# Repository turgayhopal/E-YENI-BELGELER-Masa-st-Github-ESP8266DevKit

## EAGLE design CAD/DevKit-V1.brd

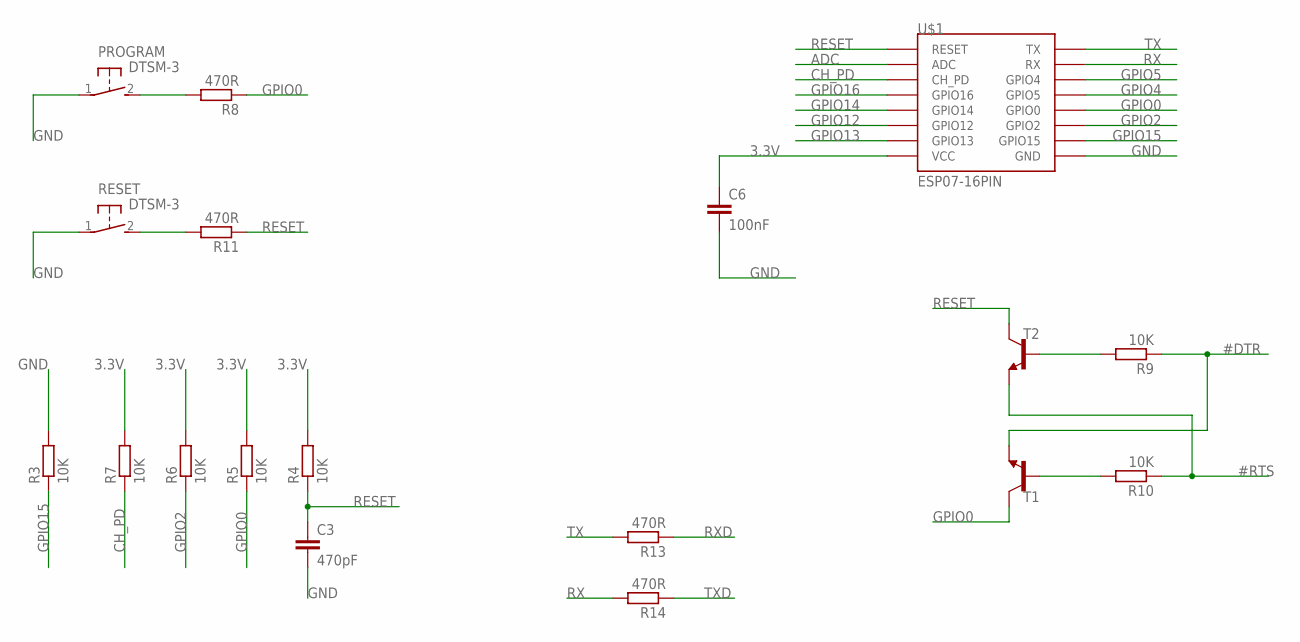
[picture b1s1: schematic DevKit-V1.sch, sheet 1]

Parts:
C3: 470pF; C0805
C6: 100nF; C0805
PROGRAM: DTSM-3
R3, R4, R5, R6, R7, R9, R10: 10K; R0805
R8, R11, R13, R14: 470R; R0805
RESET: DTSM-3
T1, T2: -NPN-SOT23-EBC; SOT23-EBC
U$1: ESP07-16PIN

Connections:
3.3V: C6.1, R4.2, R5.2, R6.2, R7.2, U$1.VCC; also elsewhere on the board
#DTR: R9.1, T1.E; also elsewhere on the board
#RTS: R10.1, T2.E; also elsewhere on the board
ADC: U$1.ADC
CH_PD: R7.1, U$1.CH_PD
GND: C3.2, C6.2, PROGRAM.1, R3.2, RESET.1, U$1.GND; also elsewhere on the board
GPIO0: R5.1, R8.1, T1.C, U$1.GPIO0
GPIO2: R6.1, U$1.GPIO2
GPIO4: U$1.GPIO5; also elsewhere on the board
GPIO5: U$1.GPIO4; also elsewhere on the board
GPIO12: U$1.GPIO12; also elsewhere on the board
GPIO13: U$1.GPIO13; also elsewhere on the board
GPIO14: U$1.GPIO14; also elsewhere on the board
GPIO15: R3.1, U$1.GPIO15; also elsewhere on the board
GPIO16: U$1.GPIO16
unnamed: PROGRAM.2, R8.2
unnamed: R11.2, RESET.2
unnamed: R10.2, T1.B
unnamed: R9.2, T2.B
RESET: C3.1, R4.1, R11.1, T2.C, U$1.REST (RESET)
RX: R14.2, U$1.RX
RXD: R13.1; also elsewhere on the board
TX: R13.2, U$1.TX
TXD: R14.1; also elsewhere on the board

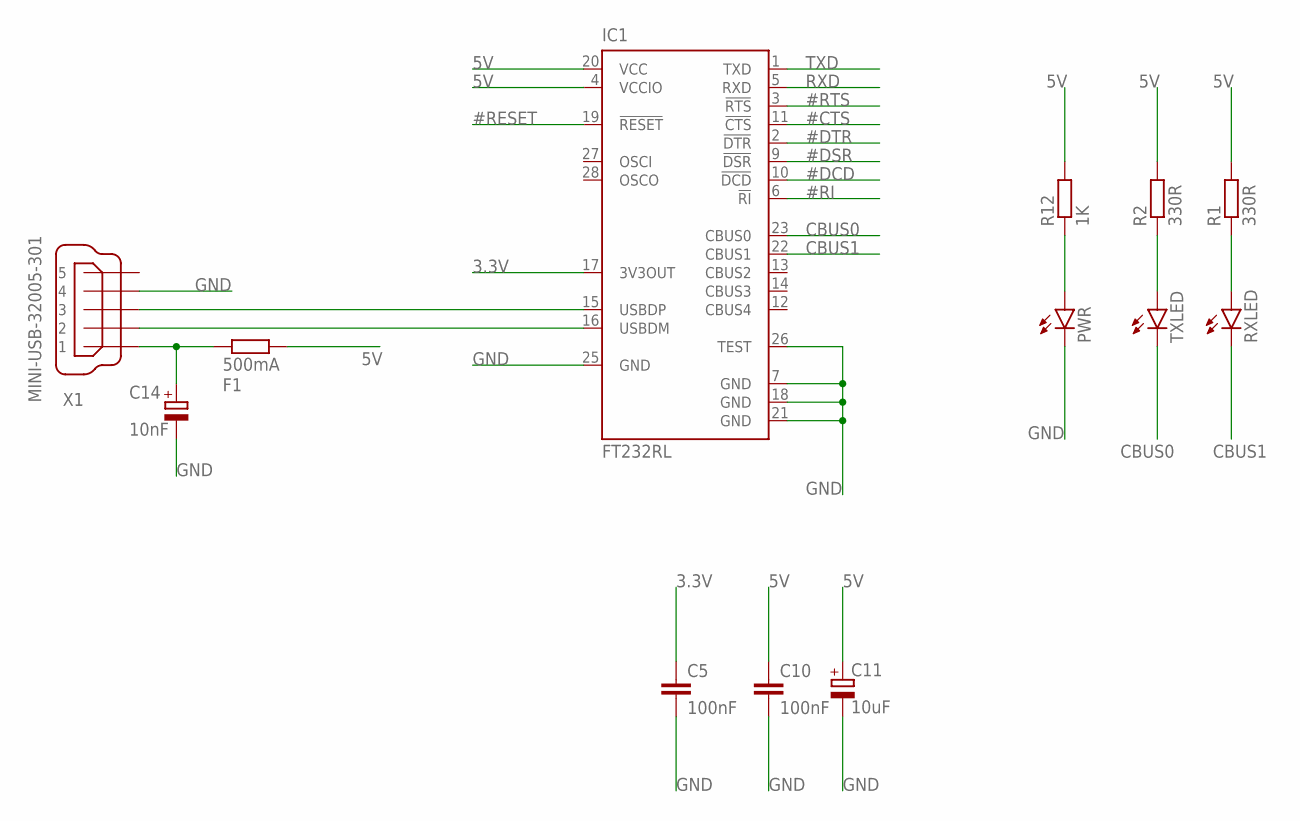
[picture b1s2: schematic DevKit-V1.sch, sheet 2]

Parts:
C5, C10: 100nF; C0805
C11: 10uF; SMC_A
C14: 10nF; SMC_A
F1: 500mA; R0805
IC1: FT232RL; SSOP28
PWR: LEDCHIP-LED0805; CHIP-LED0805
R1, R2: 330R; R0805
R12: 1K; R0805
RXLED: LEDCHIP-LED0805; CHIP-LED0805
TXLED: LEDCHIP-LED0805; CHIP-LED0805
X1: MINI-USB-32005-301; 32005-301

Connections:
3.3V: C5.1, IC1.17 (3V3OUT); also elsewhere on the board
5V: C10.1, C11.+, F1.2, IC1.4 (VCCIO), IC1.20 (VCC), R1.2, R2.2, R12.2; also elsewhere on the board
#CTS: IC1.11 (!CTS)
#DCD: IC1.10 (!DCD)
#DSR: IC1.9 (!DSR)
#DTR: IC1.2 (!DTR); also elsewhere on the board
#RESET: IC1.19 (!RESET)
#RI: IC1.6 (!RI)
#RTS: IC1.3 (!RTS); also elsewhere on the board
CBUS0: IC1.23 (CBUS0), TXLED.C
CBUS1: IC1.22 (CBUS1), RXLED.C
GND: C5.2, C10.2, C11.-, C14.-, IC1.7 (GND), IC1.18 (GND), IC1.21 (GND), IC1.25 (GND), IC1.26 (TEST), PWR.C, X1.4; also elsewhere on the board
unnamed: IC1.15 (USBDP), X1.3
unnamed: IC1.16 (USBDM), X1.2
unnamed: C14.+, F1.1, X1.1
unnamed: R1.1, RXLED.A
unnamed: R2.1, TXLED.A
unnamed: PWR.A, R12.1
RXD: IC1.5 (RXD); also elsewhere on the board
TXD: IC1.1 (TXD); also elsewhere on the board

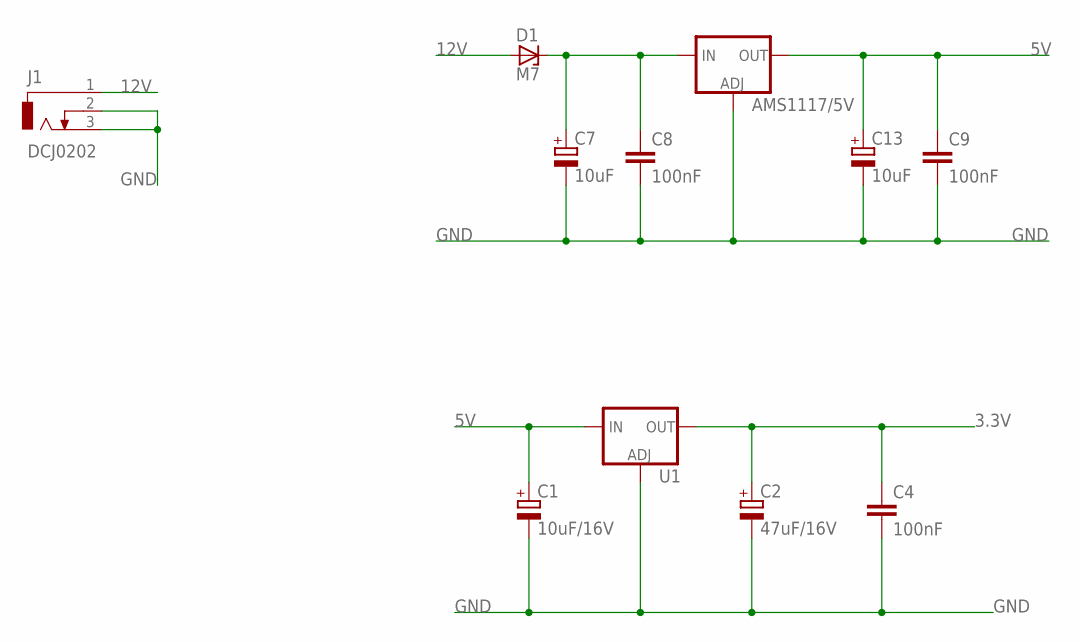
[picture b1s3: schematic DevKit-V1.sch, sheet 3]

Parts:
AMS1117/5V: V_REG_LM1117SOT223; SOT223
C1: 10uF/16V; 153CLV-0405
C2: 47uF/16V; 153CLV-0605
C4, C8, C9: 100nF; C0805
C7, C13: 10uF; 153CLV-0405
D1: M7; DO214AC
J1: DCJ0202
U1: V_REG_LM1117SOT223; SOT223

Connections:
3.3V: C2.+, C4.1, U1.2 (OUT), U1.4 (OUT); also elsewhere on the board
5V: AMS1117/5V.2 (OUT), AMS1117/5V.4 (OUT), C1.+, C9.1, C13.+, U1.3 (IN); also elsewhere on the board
12V: D1.A, J1.1
GND: AMS1117/5V.1 (ADJ), C1.-, C2.-, C4.2, C7.-, C8.2, C9.2, C13.-, J1.2, J1.3, U1.1 (ADJ); also elsewhere on the board
unnamed: AMS1117/5V.3 (IN), C7.+, C8.1, D1.C

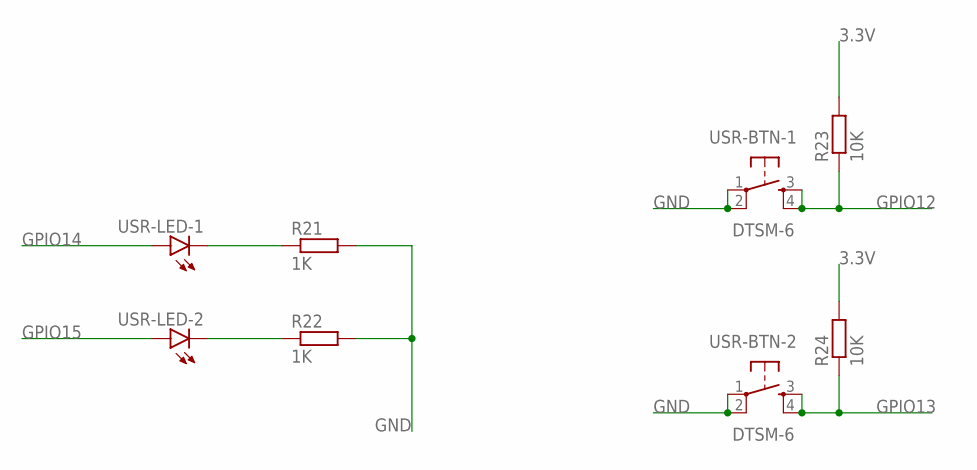
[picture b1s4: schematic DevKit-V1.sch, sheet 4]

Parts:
R21, R22: 1K; R0805
R23, R24: 10K; R0805
USR-BTN-1, USR-BTN-2: DTSM-6
USR-LED-1, USR-LED-2: LED5MM

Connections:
3.3V: R23.2, R24.2; also elsewhere on the board
GND: R21.2, R22.2, USR-BTN-1.1, USR-BTN-1.2, USR-BTN-2.1, USR-BTN-2.2; also elsewhere on the board
GPIO12: R23.1, USR-BTN-1.3, USR-BTN-1.4; also elsewhere on the board
GPIO13: R24.1, USR-BTN-2.3, USR-BTN-2.4; also elsewhere on the board
GPIO14: USR-LED-1.A; also elsewhere on the board
GPIO15: USR-LED-2.A; also elsewhere on the board
unnamed: R21.1, USR-LED-1.K (C)
unnamed: R22.1, USR-LED-2.K (C)

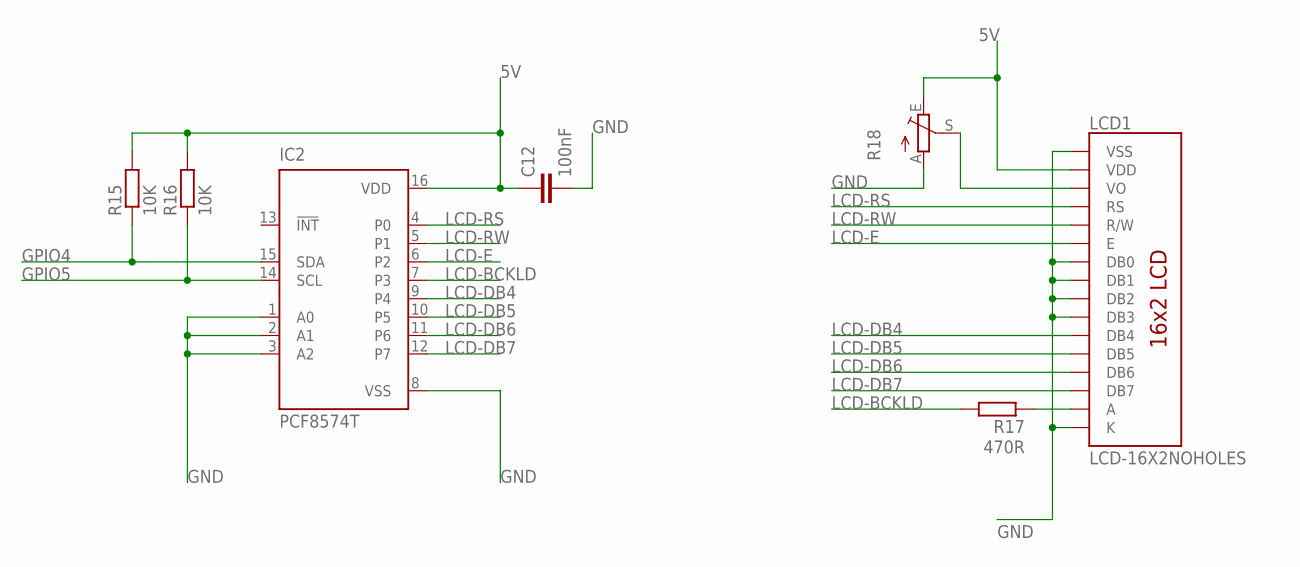
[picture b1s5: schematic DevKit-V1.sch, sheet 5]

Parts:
C12: 100nF; C0805
IC2: PCF8574T; SO16W
LCD1: LCD-16X2NOHOLES; LCD-16X2_NOHOLESNOSILK
R15, R16: 10K; R0805
R17: 470R; R0805
R18: TRIM_EU-CA6V; CA6V

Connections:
5V: C12.1, IC2.16 (VDD), LCD1.2 (VDD), R15.2, R16.2, R18.E; also elsewhere on the board
GND: C12.2, IC2.1 (A0), IC2.2 (A1), IC2.3 (A2), IC2.8 (VSS), LCD1.1 (VSS), LCD1.7 (DB0), LCD1.8 (DB1), LCD1.9 (DB2), LCD1.10 (DB3), LCD1.16 (K), R18.A; also elsewhere on the board
GPIO4: IC2.15 (SDA), R15.1; also elsewhere on the board
GPIO5: IC2.14 (SCL), R16.1; also elsewhere on the board
LCD-BCKLD: IC2.7 (P3), R17.2
LCD-DB4: IC2.9 (P4), LCD1.11 (DB4)
LCD-DB5: IC2.10 (P5), LCD1.12 (DB5)
LCD-DB6: IC2.11 (P6), LCD1.13 (DB6)
LCD-DB7: IC2.12 (P7), LCD1.14 (DB7)
LCD-E: IC2.6 (P2), LCD1.6 (E)
LCD-RS: IC2.4 (P0), LCD1.4 (RS)
LCD-RW: IC2.5 (P1), LCD1.5 (R/W)
unnamed: LCD1.15 (A), R17.1
unnamed: LCD1.3 (VO), R18.S

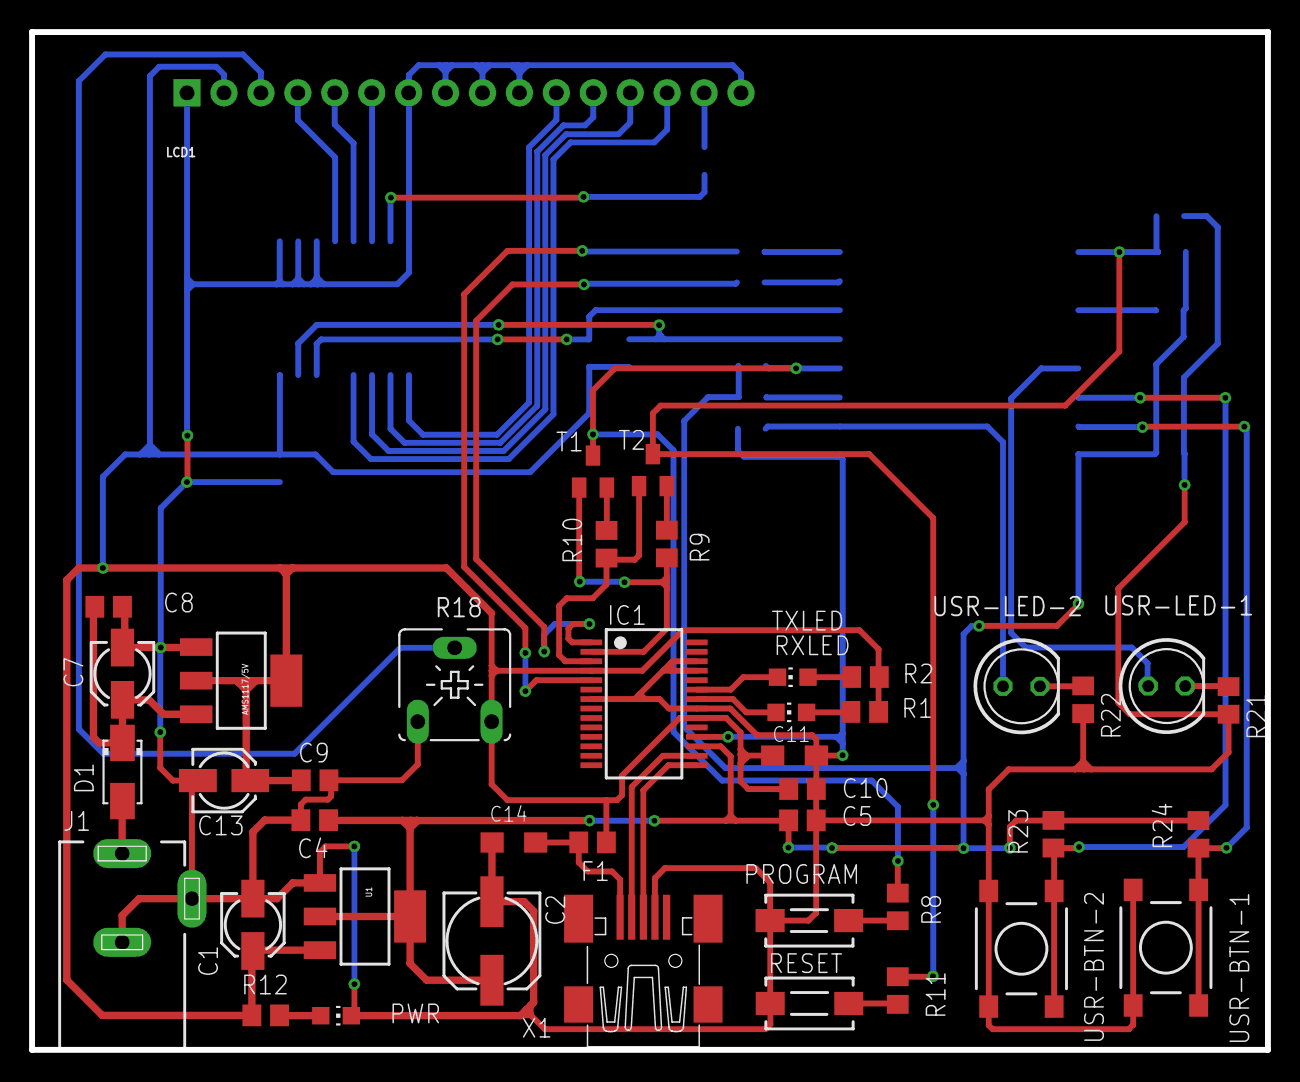
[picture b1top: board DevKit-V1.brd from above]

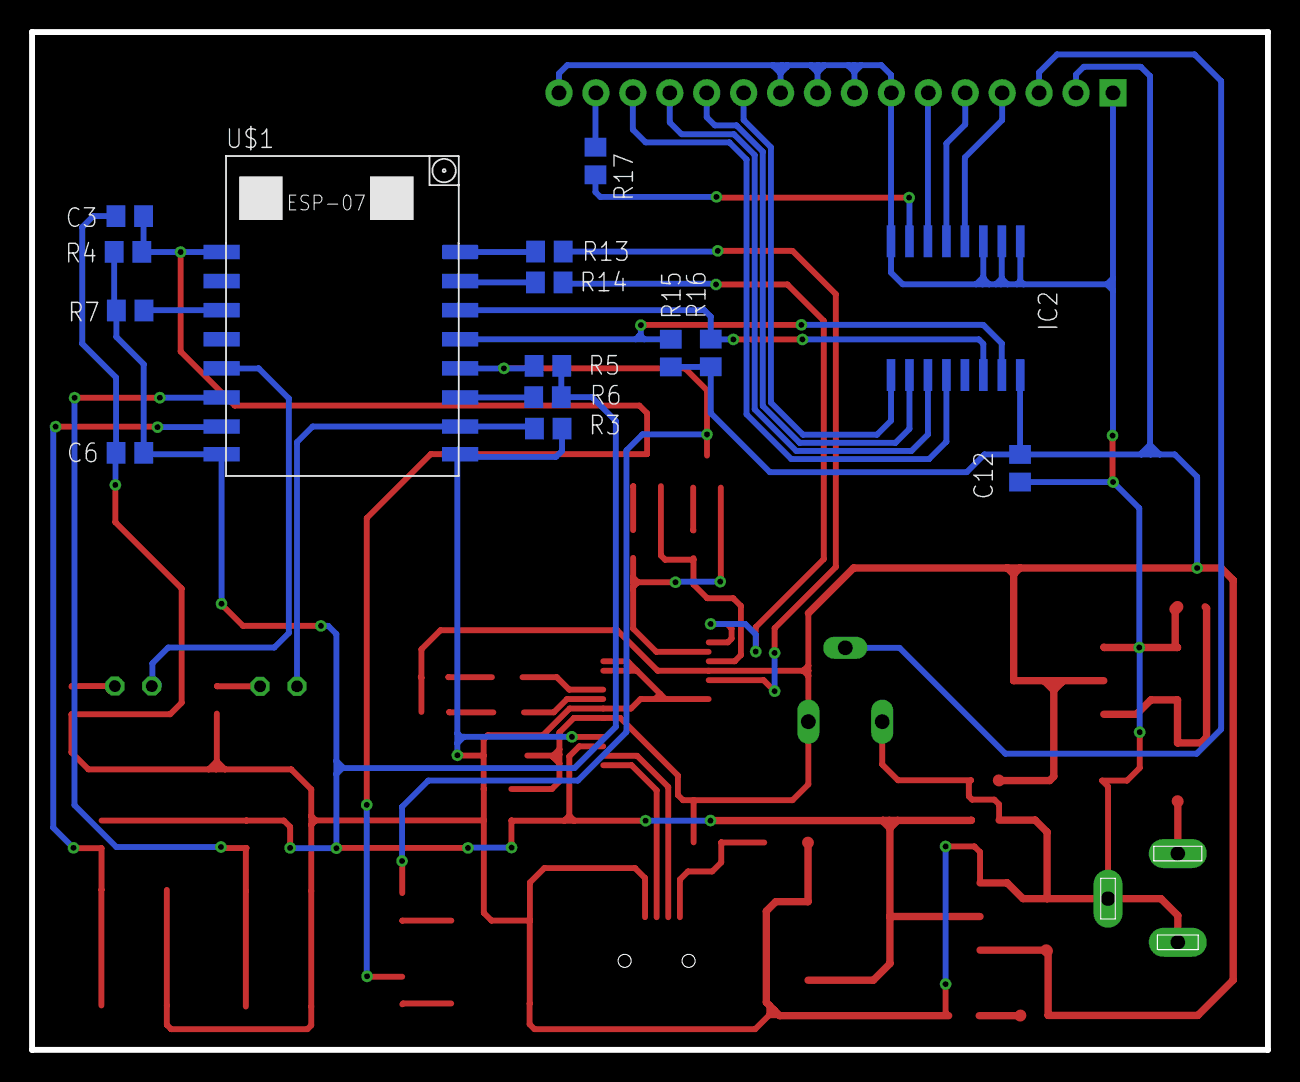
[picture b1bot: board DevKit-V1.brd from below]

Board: 2 copper layers, 85.0 x 70.0 mm, 57 parts (15 on the bottom side), 45 nets.

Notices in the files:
parts and their libraries:
SparkFun-IC-Power: Licensing: Creative Commons ShareAlike 4.0 International - https://creativecommons.org/licenses/by-sa/4.0
